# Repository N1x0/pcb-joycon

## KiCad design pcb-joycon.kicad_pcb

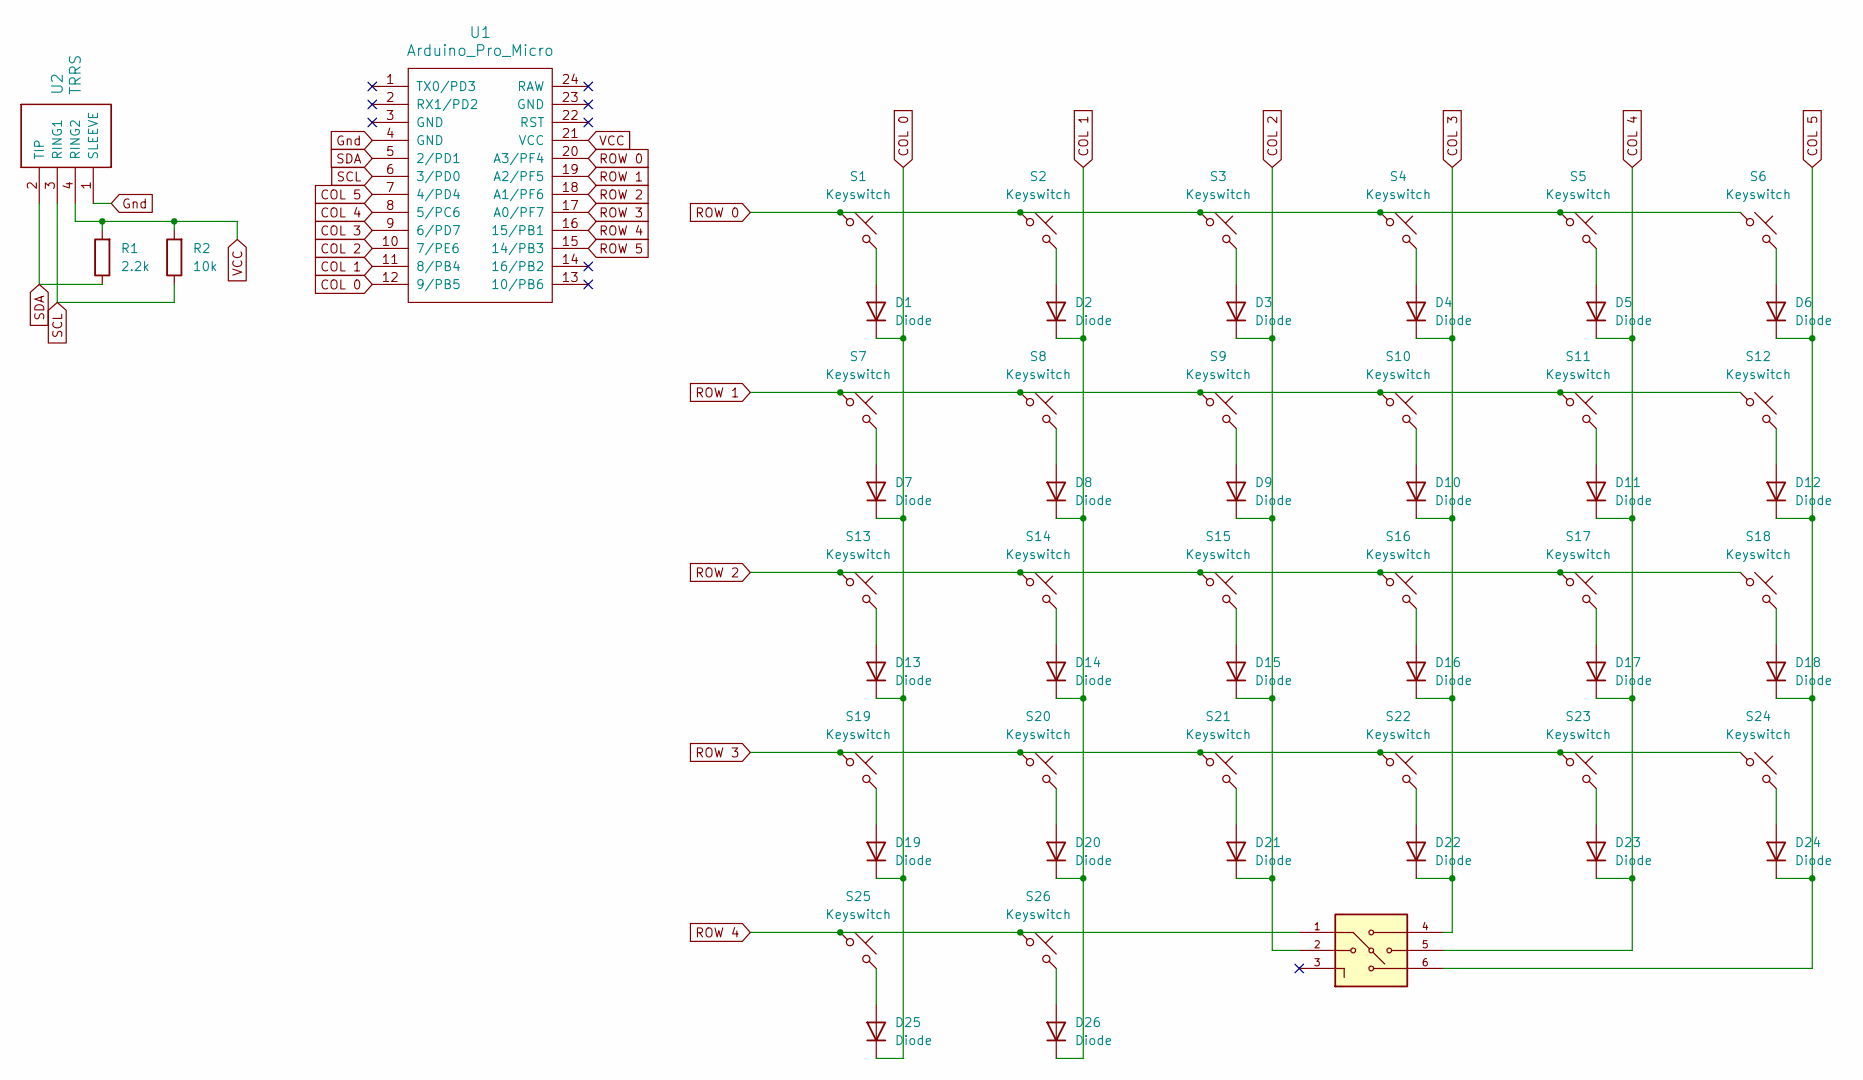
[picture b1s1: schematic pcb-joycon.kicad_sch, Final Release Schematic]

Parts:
D1: Diode; R_0201_0603Metric
D2, D3, D4, D5, D6, D7, D8, D9, D10, D11, D12, D13, D14, D15, D16, D17, D18, D19, D20, D21, D22, D23, D24, D25, D26: Diode; Diode_SOD-123
R1: 2.2k; R_0201_0603Metric
R2: 10k; R_0201_0603Metric
S1, S2, S3, S4, S5, S6, S7, S8, S9, S10, S11, S12, S13, S14, S15, S16, S17, S18, S19, S20, S21, S22, S23, S24: Keyswitch; Hotswap_MX_1.00u
S25, S26: Keyswitch; Hotswap_Choc_V2_1.00u
S27: JS5208; SW_JS5208; PARTREV D; DigiKey_Part_Number EG4561-ND
U1: Arduino_Pro_Micro
U2: TRRS; TRRS_PJ-320A

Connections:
COL 0: D1.1 (K), D7.1 (K), D13.1 (K), D19.1 (K), D25.1 (K), U1.12 (9/PB5)
COL 1: D2.1 (K), D8.1 (K), D14.1 (K), D20.1 (K), D26.1 (K), U1.11 (8/PB4)
COL 2: D3.1 (K), D9.1 (K), D15.1 (K), D21.1 (K), S27.2, U1.10 (7/PE6)
COL 3: D4.1 (K), D10.1 (K), D16.1 (K), D22.1 (K), S27.4, U1.9 (6/PD7)
COL 4: D5.1 (K), D11.1 (K), D17.1 (K), D23.1 (K), S27.5, U1.8 (5/PC6)
COL 5: D6.1 (K), D12.1 (K), D18.1 (K), D24.1 (K), S27.6, U1.7 (4/PD4)
Gnd: U1.4 (GND), U2.1 (SLEEVE)
unnamed: D1.2 (A), S1.2
unnamed: D2.2 (A), S2.2
unnamed: D3.2 (A), S3.2
unnamed: D4.2 (A), S4.2
unnamed: D5.2 (A), S5.2
unnamed: D6.2 (A), S6.2
unnamed: D7.2 (A), S7.2
unnamed: D8.2 (A), S8.2
unnamed: D9.2 (A), S9.2
unnamed: D10.2 (A), S10.2
unnamed: D11.2 (A), S11.2
unnamed: D12.2 (A), S12.2
unnamed: D13.2 (A), S13.2
unnamed: D14.2 (A), S14.2
unnamed: D15.2 (A), S15.2
unnamed: D16.2 (A), S16.2
unnamed: D17.2 (A), S17.2
unnamed: D18.2 (A), S18.2
unnamed: D19.2 (A), S19.2
unnamed: D20.2 (A), S20.2
unnamed: D21.2 (A), S21.2
unnamed: D22.2 (A), S22.2
unnamed: D23.2 (A), S23.2
unnamed: D24.2 (A), S24.2
unnamed: D25.2 (A), S25.2
unnamed: D26.2 (A), S26.2
ROW 0: S1.1, S2.1, S3.1, S4.1, S5.1, S6.1, U1.20 (A3/PF4)
ROW 1: S7.1, S8.1, S9.1, S10.1, S11.1, S12.1, U1.19 (A2/PF5)
ROW 2: S13.1, S14.1, S15.1, S16.1, S17.1, S18.1, U1.18 (A1/PF6)
ROW 3: S19.1, S20.1, S21.1, S22.1, S23.1, S24.1, U1.17 (A0/PF7)
ROW 4: S25.1, S26.1, S27.1, U1.16 (15/PB1)
ROW 5: U1.15 (14/PB3)
SCL: R2.1, U1.6 (3/PD0), U2.3 (RING1)
SDA: R1.1, U1.5 (2/PD1), U2.2 (TIP)
VCC: R1.2, R2.2, U1.21 (VCC), U2.4 (RING2)

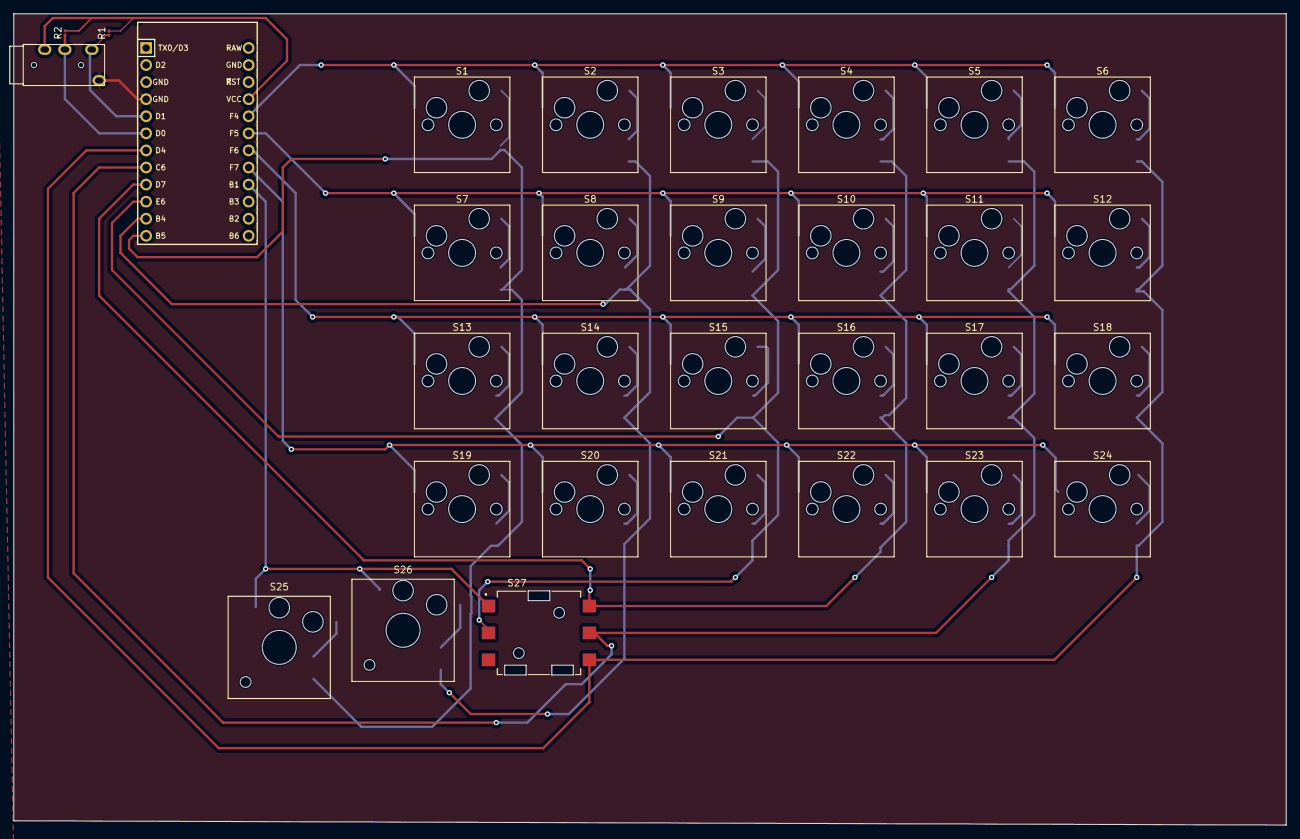
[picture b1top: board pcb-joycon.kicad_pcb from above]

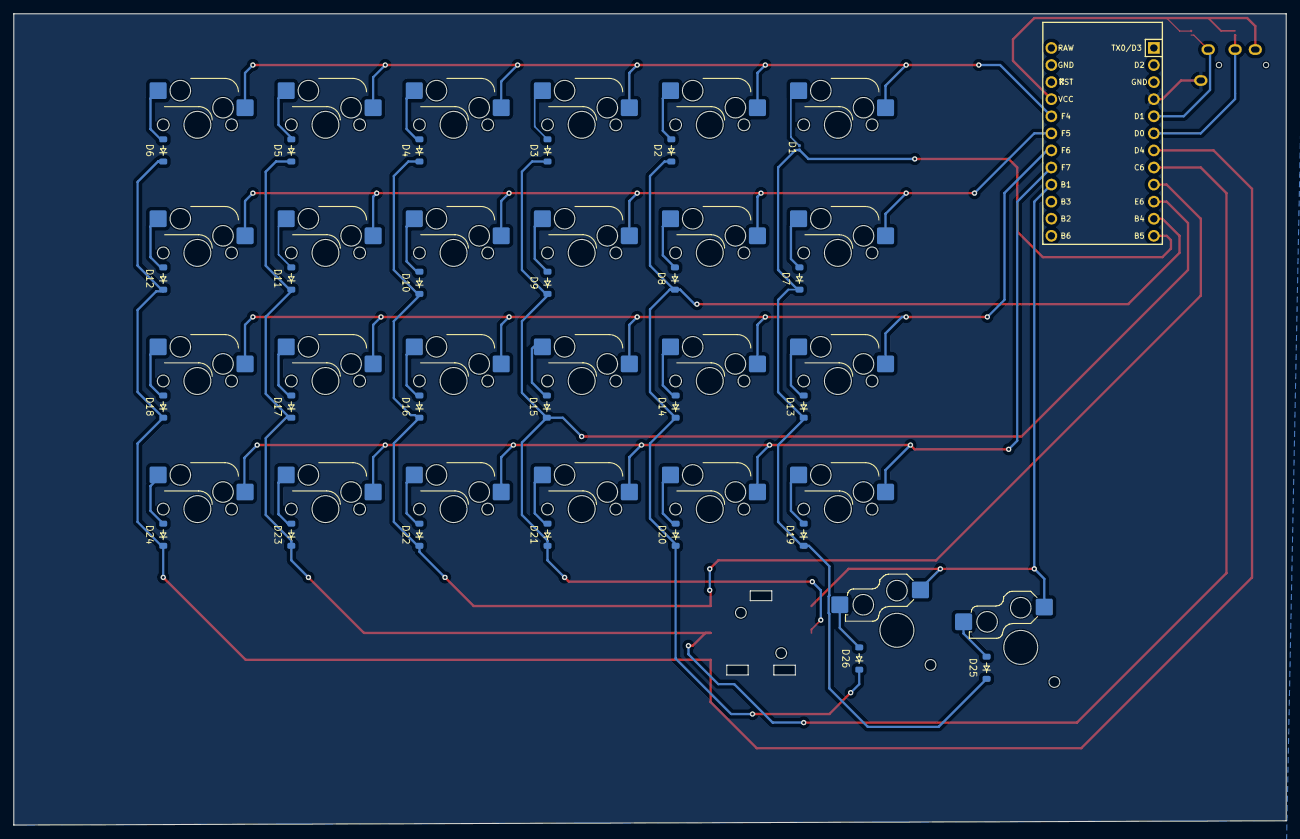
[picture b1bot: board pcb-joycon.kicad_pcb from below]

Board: 2 copper layers, 189.2 x 120.6 mm, 57 parts (26 on the bottom side), 41 nets.

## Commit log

2023-12-18 minor edit
